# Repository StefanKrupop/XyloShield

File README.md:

XyloShield DMX
==============

The XyloShield DMX is a simple Shield for Arduinos like the Uno that has two functions: On the one hand, it hosts a RFM26W radio module and the necessary level shifting to use it with a 5 V Arduino. On the other hand (and because enough space was left...), it contains an RDM capable DMX-512 transceiver.
Both functions are completely separate, so the board can also be populated only partially to support the function you want.
The board was designed using KiCad (my first project with that package, so be warned!).

There is also an Arduino library for the shield: XyloLibrary (https://github.com/StefanKrupop/XyloLibrary)

Radio
-----

The main functionality (and where its name comes from) of the board is to be able to send radio packets to "Xylobands" LED bracelets in order to study the proprietary protocol used by them. An 868 MHz RFM26W radio module was selected as it uses a compatible radio controller to that one on the Xylobands.
As this part is 3.3 V only, a 74HC4050 was added as a level shifter for the 5 V Arduino.
The chip can be disabled by removing the "CS" jumper, which disconnects the Arduino pin from the shield. A pull-up resistor then keeps the radio module disabled.

The radio module uses SPI and is connected to the following Arduino pins:
D3 <- nIRQ
D4 -> SDN
D10 -> nSEL (/CS)
MISO <- SDO
MOSI -> SDI
SCK -> SCK

The radio part is comprised of the following components (that can be left unpopulated if you do not need this functionality):
C1, C3, J6, J7, R5, U1, U3

DMX-512
-------

The DMX part can be used to build a DMX-512 sender, receiver or an RDM capable device. It uses a standard RS485 transceiver and a "Line Bias Network" to be able to support RDM.
If the DMX part should be used as a receiver (with or without RDM), resistors R1 to R3 should be left unpopulated, as the Line Bias Network should only be used by a DMX sender.
Jumpers J3 to J5 can be used to disconnect the Arduino pins from the shield.

**ATTENTION**: When using e.g. the Arduino Uno, J5 needs to be open to be able to upload a sketch!

The DMX part uses the UART and is connected to the following Arduino pins:
D0 <- RXD
D1 -> TXD
D2 -> Receive/Transmit select

The DMX part is comprised of the following components (that can be left unpopulated if you do not need this functionality):
C2, J1, J2, J3, J4, J5, R1, R2, R3, R4, U2

BOM
---

| Part      | Value                      | Conrad Electronics order nr. | 
|-----------|----------------------------|------------------------------|
| C1-C3     | 100 nF, 25 V, 0603         | 1279656                      |
| J1        | Neutrik NC3MAAH            | 651105                       |
| J2        | Neutrik NC3FAAH1           | 651095                       |
| J3-J5, J7 | 2,54 mm pin header         | 1390109                      |
| J6        | RP-SMA connector           | 1565639                      |
| R1, R3    | 562 Ohms, 0603             | 437643                       |
| R2        | 133 Ohms, 0603             | 433625                       |
| R4, R5    | 10 k, 0603                 | 1208549                      |
| U1        | 74HC4050, SOIC-16          | 1015779                      |
| U2        | SN75176, SOIC-8            | 1048058                      |
| U3        | RFM26W                     | -                            |
| -         | Matching antenna           | 673977                       |
| -         | 32 pins 2,54 mm pin header | 1390109                      |
| -         | 2x3 pins socket            | 1492284                      |
| -         | 4 jumper caps              | 1560848                      |

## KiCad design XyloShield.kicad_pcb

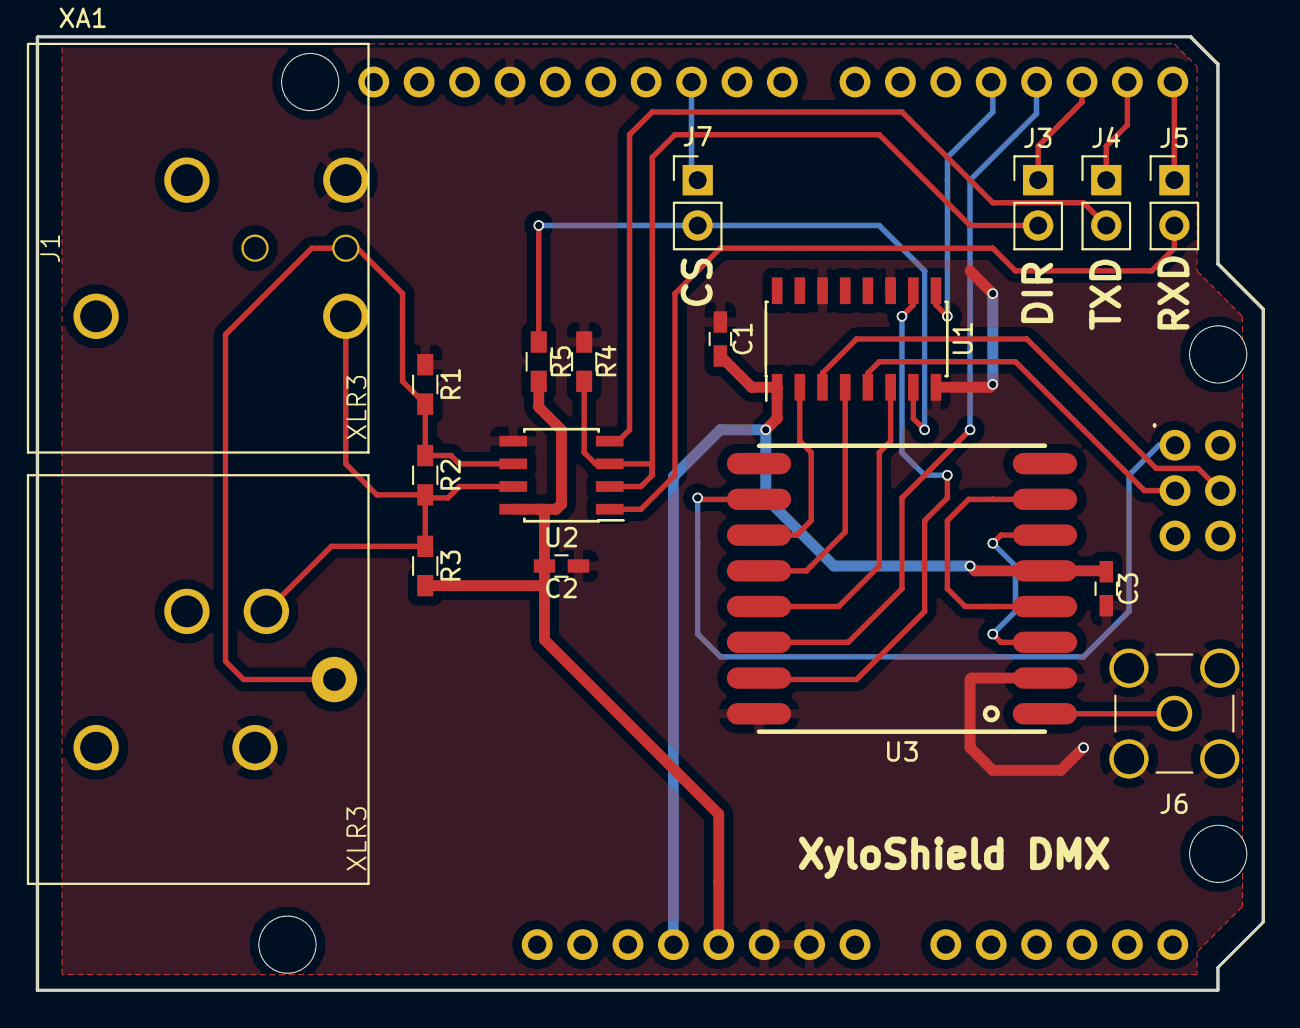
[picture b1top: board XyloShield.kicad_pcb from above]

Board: 2 copper layers, 68.6 x 53.3 mm, 19 parts (0 on the bottom side), 25 nets.

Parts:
C1, C2, C3: 100n; C_0603_HandSoldering
J1: XLR3; XLR-NC3MA
J2: XLR3; XLR-NC3FA
J3, J4, J5, J7: Conn_01x02; Pin_Header_Straight_1x02_Pitch2.54mm
J6: Conn_Coaxial; SMA_THT_Jack_Straight
R1, R3: 562; R_0603_HandSoldering
R2: 133; R_0603_HandSoldering
R4, R5: 10k; R_0603_HandSoldering
U1: 4050; SOIC-16_3.9x9.9mm_Pitch1.27mm
U2: MAX485E; SOIC-8_3.9x4.9mm_Pitch1.27mm
U3: RFM26W
XA1: Arduino_Uno_Shield

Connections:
+3V3: C1.1, C3.1, U1.1, U3.5, XA1.3V3
+5V: C2.1, R3.2, R5.2, U2.8, XA1.5V1
GND: C1.2, C2.2, C3.2, J1.1, J2.1, J6.2, R1.1, R4.2, U1.8, U1.11, U1.14, U2.5, U3.2, U3.16, XA1.GND1, XA1.GND2, XA1.GND3
unnamed: J1.2, J2.2, R2.2, R3.1, U2.7
unnamed: J1.3, J2.3, R1.2, R2.1, U2.6
unnamed: J3.1, XA1.D2
unnamed: J3.2, R4.1, U2.2, U2.3
unnamed: J4.1, XA1.D1
unnamed: J4.2, U2.4
unnamed: J5.1, XA1.D0
unnamed: J5.2, U2.1
unnamed: J6.1, U3.1
unnamed: J7.1, XA1.D10
unnamed: J7.2, R5.1, U1.7
unnamed: U1.2, U3.11
unnamed: U1.3, XA1.MOSI
unnamed: U1.4, U3.12
unnamed: U1.5, XA1.SCK
unnamed: U1.6, U3.13
unnamed: U1.9, XA1.D4
unnamed: U1.10, U3.15
unnamed: U3.3, U3.6
unnamed: U3.4, U3.7
unnamed: U3.10, XA1.MISO
unnamed: U3.14, XA1.D3

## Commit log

2018-05-11 Some cleanup (adjusted track widths, used finer grid for component placement)
2018-05-11 - Fixed orientation of J7 - Added some more silkscreen text - Exported Gerbers
2018-06-16 Added README.md with description of project and pinouts
2018-06-16 - Added BOM with order numbers for Conrad electronics - Added PDF of schematic
2018-06-17 Added missing "ISP" socket to BOM
2018-07-09 Added link to XyloLibrary
